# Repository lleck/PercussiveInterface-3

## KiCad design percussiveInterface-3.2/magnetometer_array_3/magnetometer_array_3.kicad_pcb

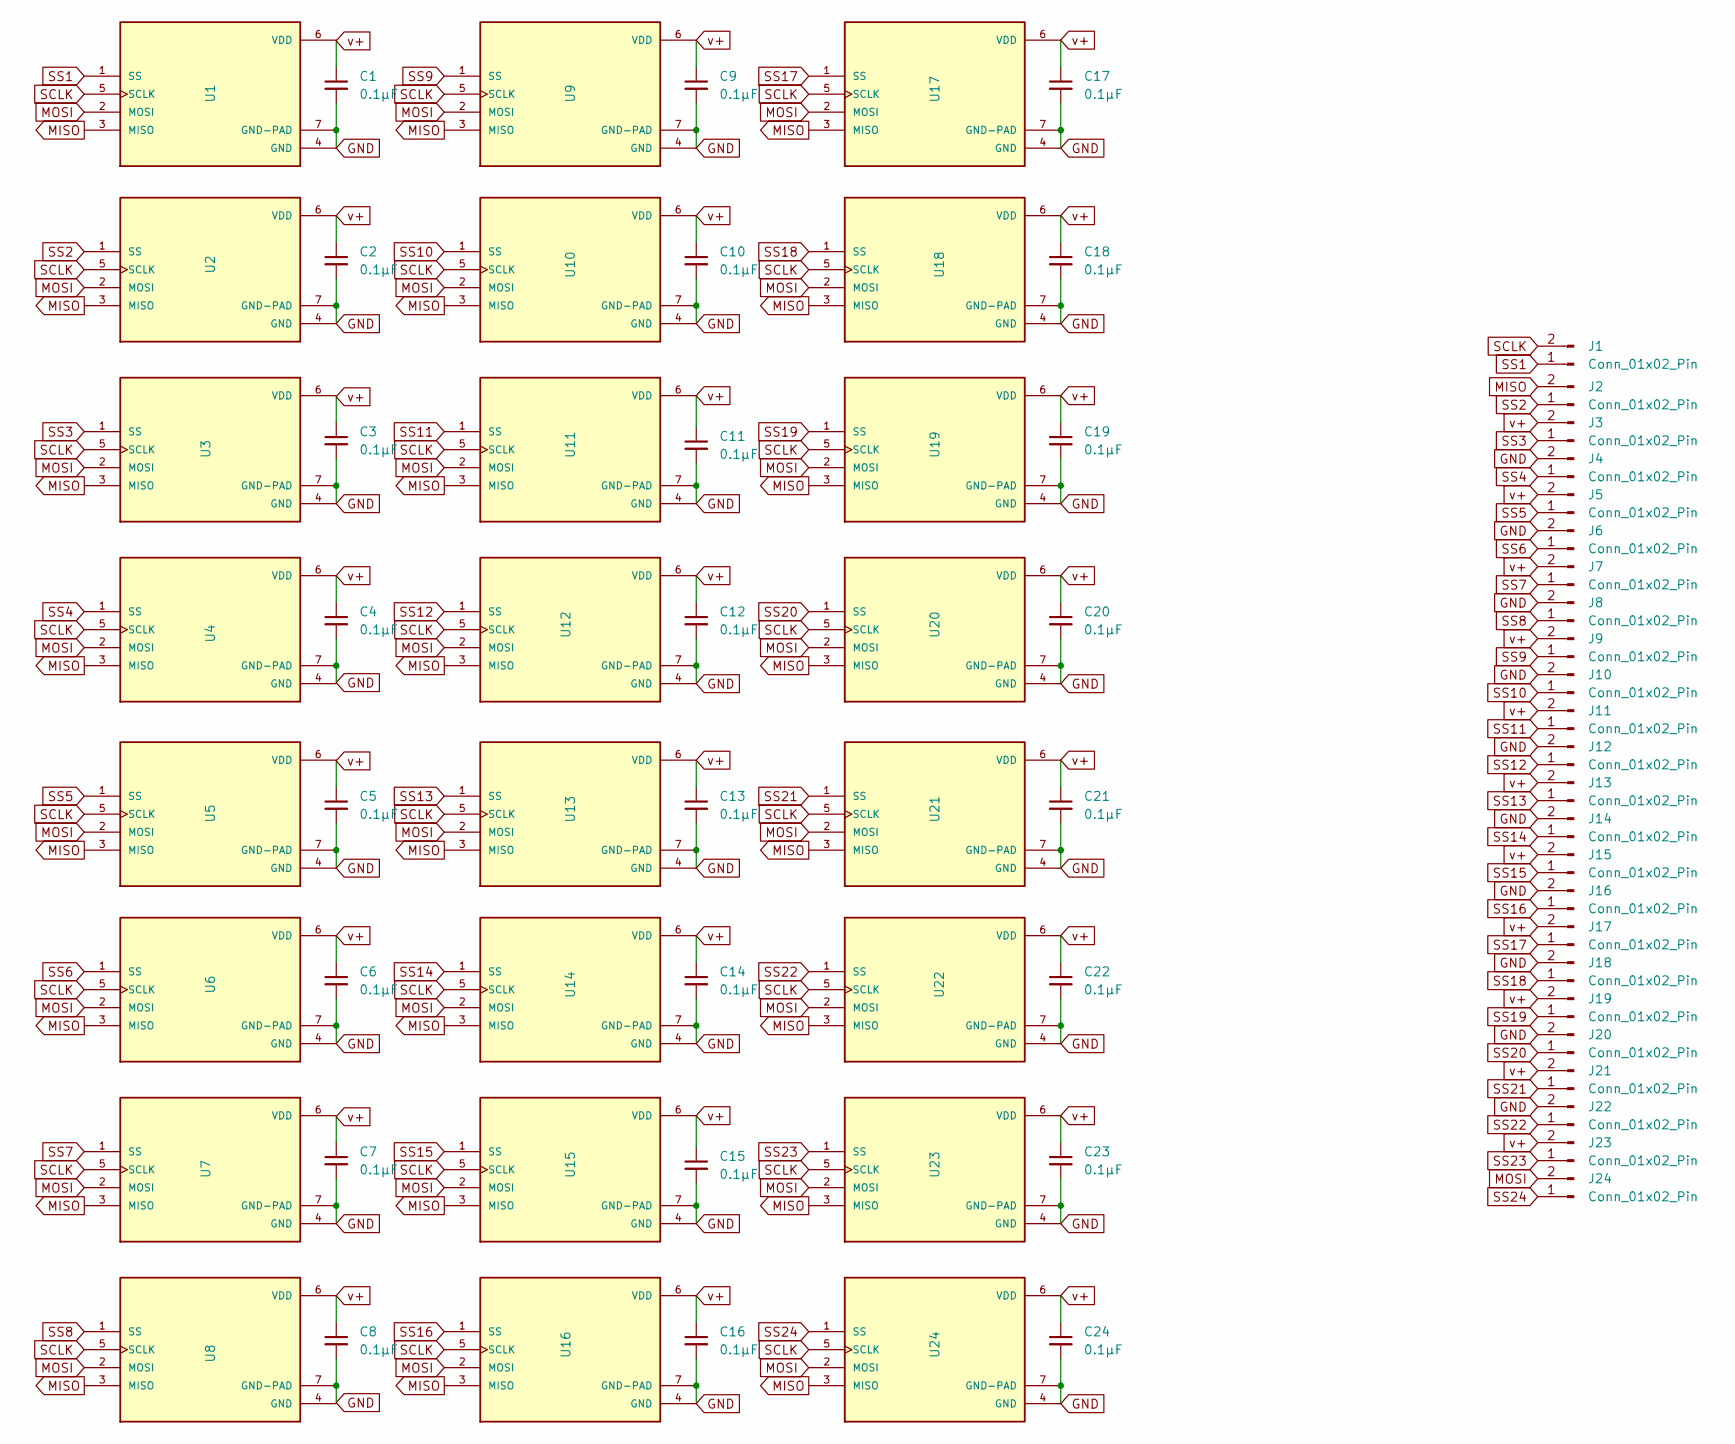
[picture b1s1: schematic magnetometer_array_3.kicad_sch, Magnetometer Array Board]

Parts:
C1, C2, C3, C4, C5, C6, C7, C8, C9, C10, C11, C12, C13, C14, C15, C16, C17, C18, C19, C20, C21, C22, C23, C24: 0.1µF; C_0201_0603Metric
J1, J2, J3, J4, J5, J6, J7, J8, J9, J10, J11, J12, J13, J14, J15, J16, J17, J18, J19, J20, J21, J22, J23, J24: Conn_01x02_Pin; mill_max 328-HORIZONTAL SURFACE MOUNT HEADER
U1, U2, U3, U4, U5, U6, U7, U8, U9, U10, U11, U12, U13, U14, U15, U16, U17, U18, U19, U20, U21, U22, U23, U24: SM225-10E; NVE SM225 10E; PARTREV D

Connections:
GND: C1.2, C2.2, C3.2, C4.2, C5.2, C6.2, C7.2, C8.2, C9.2, C10.2, C11.2, C12.2, C13.2, C14.2, C15.2, C16.2, C17.2, C18.2, C19.2, C20.2, C21.2, C22.2, C23.2, C24.2, J4.2, J6.2, J8.2, J10.2, J12.2, J14.2, J16.2, J18.2, J20.2, J22.2, U1.4 (GND), U1.7 (GND-PAD), U2.4 (GND), U2.7 (GND-PAD), U3.4 (GND), U3.7 (GND-PAD), U4.4 (GND), U4.7 (GND-PAD), U5.4 (GND), U5.7 (GND-PAD), U6.4 (GND), U6.7 (GND-PAD), U7.4 (GND), U7.7 (GND-PAD), U8.4 (GND), U8.7 (GND-PAD), U9.4 (GND), U9.7 (GND-PAD), U10.4 (GND), U10.7 (GND-PAD), U11.4 (GND), U11.7 (GND-PAD), U12.4 (GND), U12.7 (GND-PAD), U13.4 (GND), U13.7 (GND-PAD), U14.4 (GND), U14.7 (GND-PAD), U15.4 (GND), U15.7 (GND-PAD), U16.4 (GND), U16.7 (GND-PAD), U17.4 (GND), U17.7 (GND-PAD), U18.4 (GND), U18.7 (GND-PAD), U19.4 (GND), U19.7 (GND-PAD), U20.4 (GND), U20.7 (GND-PAD), U21.4 (GND), U21.7 (GND-PAD), U22.4 (GND), U22.7 (GND-PAD), U23.4 (GND), U23.7 (GND-PAD), U24.4 (GND), U24.7 (GND-PAD)
MISO: J2.2, U1.3 (MISO), U2.3 (MISO), U3.3 (MISO), U4.3 (MISO), U5.3 (MISO), U6.3 (MISO), U7.3 (MISO), U8.3 (MISO), U9.3 (MISO), U10.3 (MISO), U11.3 (MISO), U12.3 (MISO), U13.3 (MISO), U14.3 (MISO), U15.3 (MISO), U16.3 (MISO), U17.3 (MISO), U18.3 (MISO), U19.3 (MISO), U20.3 (MISO), U21.3 (MISO), U22.3 (MISO), U23.3 (MISO), U24.3 (MISO)
MOSI: J24.2, U1.2 (MOSI), U2.2 (MOSI), U3.2 (MOSI), U4.2 (MOSI), U5.2 (MOSI), U6.2 (MOSI), U7.2 (MOSI), U8.2 (MOSI), U9.2 (MOSI), U10.2 (MOSI), U11.2 (MOSI), U12.2 (MOSI), U13.2 (MOSI), U14.2 (MOSI), U15.2 (MOSI), U16.2 (MOSI), U17.2 (MOSI), U18.2 (MOSI), U19.2 (MOSI), U20.2 (MOSI), U21.2 (MOSI), U22.2 (MOSI), U23.2 (MOSI), U24.2 (MOSI)
SCLK: J1.2, U1.5 (SCLK), U2.5 (SCLK), U3.5 (SCLK), U4.5 (SCLK), U5.5 (SCLK), U6.5 (SCLK), U7.5 (SCLK), U8.5 (SCLK), U9.5 (SCLK), U10.5 (SCLK), U11.5 (SCLK), U12.5 (SCLK), U13.5 (SCLK), U14.5 (SCLK), U15.5 (SCLK), U16.5 (SCLK), U17.5 (SCLK), U18.5 (SCLK), U19.5 (SCLK), U20.5 (SCLK), U21.5 (SCLK), U22.5 (SCLK), U23.5 (SCLK), U24.5 (SCLK)
SS1: J1.1, U1.1 (SS)
SS2: J2.1, U2.1 (SS)
SS3: J3.1, U3.1 (SS)
SS4: J4.1, U4.1 (SS)
SS5: J5.1, U5.1 (SS)
SS6: J6.1, U6.1 (SS)
SS7: J7.1, U7.1 (SS)
SS8: J8.1, U8.1 (SS)
SS9: J9.1, U9.1 (SS)
SS10: J10.1, U10.1 (SS)
SS11: J11.1, U11.1 (SS)
SS12: J12.1, U12.1 (SS)
SS13: J13.1, U13.1 (SS)
SS14: J14.1, U14.1 (SS)
SS15: J15.1, U15.1 (SS)
SS16: J16.1, U16.1 (SS)
SS17: J17.1, U17.1 (SS)
SS18: J18.1, U18.1 (SS)
SS19: J19.1, U19.1 (SS)
SS20: J20.1, U20.1 (SS)
SS21: J21.1, U21.1 (SS)
SS22: J22.1, U22.1 (SS)
SS23: J23.1, U23.1 (SS)
SS24: J24.1, U24.1 (SS)
v+: C1.1, C2.1, C3.1, C4.1, C5.1, C6.1, C7.1, C8.1, C9.1, C10.1, C11.1, C12.1, C13.1, C14.1, C15.1, C16.1, C17.1, C18.1, C19.1, C20.1, C21.1, C22.1, C23.1, C24.1, J3.2, J5.2, J7.2, J9.2, J11.2, J13.2, J15.2, J17.2, J19.2, J21.2, J23.2, U1.6 (VDD), U2.6 (VDD), U3.6 (VDD), U4.6 (VDD), U5.6 (VDD), U6.6 (VDD), U7.6 (VDD), U8.6 (VDD), U9.6 (VDD), U10.6 (VDD), U11.6 (VDD), U12.6 (VDD), U13.6 (VDD), U14.6 (VDD), U15.6 (VDD), U16.6 (VDD), U17.6 (VDD), U18.6 (VDD), U19.6 (VDD), U20.6 (VDD), U21.6 (VDD), U22.6 (VDD), U23.6 (VDD), U24.6 (VDD)

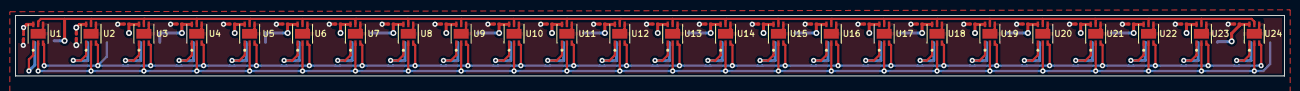
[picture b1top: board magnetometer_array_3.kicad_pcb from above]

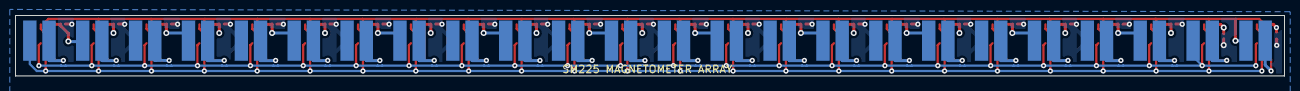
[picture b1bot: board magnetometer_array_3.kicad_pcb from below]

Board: 4 copper layers, 168.0 x 8.0 mm, 72 parts (24 on the bottom side), 29 nets.

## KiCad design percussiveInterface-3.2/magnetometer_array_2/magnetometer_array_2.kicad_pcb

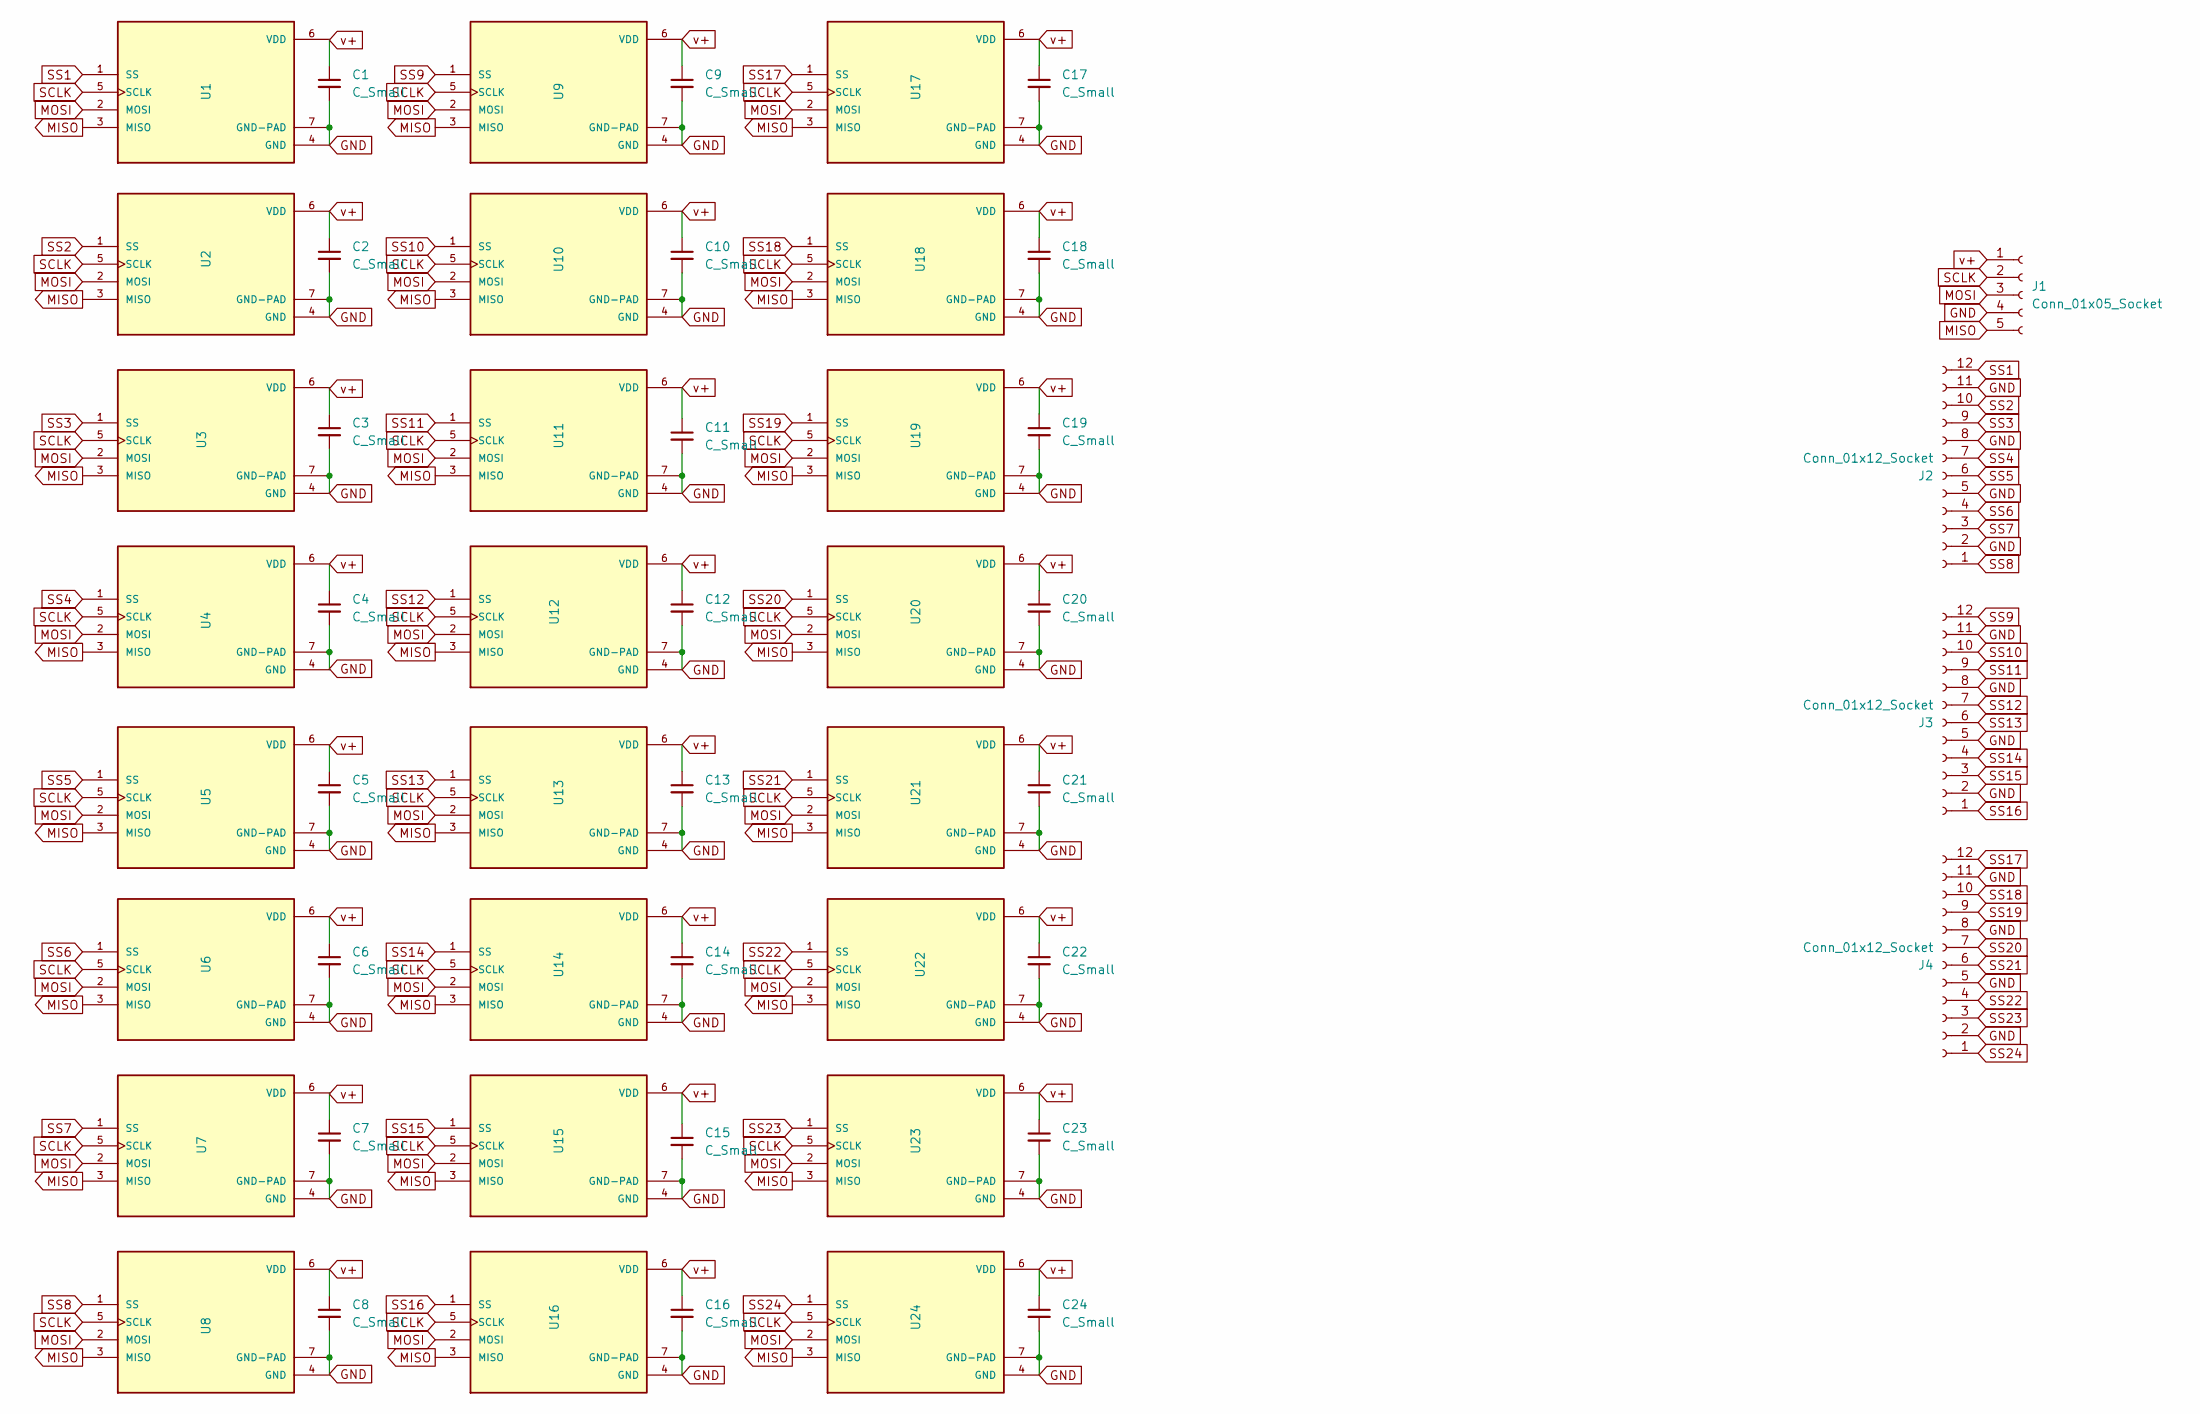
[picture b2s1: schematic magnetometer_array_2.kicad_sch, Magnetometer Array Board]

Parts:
C1, C2, C3, C4, C5, C6, C7, C8, C9, C10, C11, C12, C13, C14, C15, C16, C17, C18, C19, C20, C21, C22, C23, C24: C_Small; C_0201_0603Metric
J1: Conn_01x05_Socket; PinHeader_1x05_P2.54mm_Horizontal
J2, J3, J4: Conn_01x12_Socket; PinHeader_1x12_P2.54mm_Horizontal
U1, U2, U3, U4, U5, U6, U7, U8, U9, U10, U11, U12, U13, U14, U15, U16, U17, U18, U19, U20, U21, U22, U23, U24: SM225-10E; NVE SM225 10E; PARTREV D

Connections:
GND: C1.2, C2.2, C3.2, C4.2, C5.2, C6.2, C7.2, C8.2, C9.2, C10.2, C11.2, C12.2, C13.2, C14.2, C15.2, C16.2, C17.2, C18.2, C19.2, C20.2, C21.2, C22.2, C23.2, C24.2, J1.4, J2.2, J2.5, J2.8, J2.11, J3.2, J3.5, J3.8, J3.11, J4.2, J4.5, J4.8, J4.11, U1.4 (GND), U1.7 (GND-PAD), U2.4 (GND), U2.7 (GND-PAD), U3.4 (GND), U3.7 (GND-PAD), U4.4 (GND), U4.7 (GND-PAD), U5.4 (GND), U5.7 (GND-PAD), U6.4 (GND), U6.7 (GND-PAD), U7.4 (GND), U7.7 (GND-PAD), U8.4 (GND), U8.7 (GND-PAD), U9.4 (GND), U9.7 (GND-PAD), U10.4 (GND), U10.7 (GND-PAD), U11.4 (GND), U11.7 (GND-PAD), U12.4 (GND), U12.7 (GND-PAD), U13.4 (GND), U13.7 (GND-PAD), U14.4 (GND), U14.7 (GND-PAD), U15.4 (GND), U15.7 (GND-PAD), U16.4 (GND), U16.7 (GND-PAD), U17.4 (GND), U17.7 (GND-PAD), U18.4 (GND), U18.7 (GND-PAD), U19.4 (GND), U19.7 (GND-PAD), U20.4 (GND), U20.7 (GND-PAD), U21.4 (GND), U21.7 (GND-PAD), U22.4 (GND), U22.7 (GND-PAD), U23.4 (GND), U23.7 (GND-PAD), U24.4 (GND), U24.7 (GND-PAD)
MISO: J1.5, U1.3 (MISO), U2.3 (MISO), U3.3 (MISO), U4.3 (MISO), U5.3 (MISO), U6.3 (MISO), U7.3 (MISO), U8.3 (MISO), U9.3 (MISO), U10.3 (MISO), U11.3 (MISO), U12.3 (MISO), U13.3 (MISO), U14.3 (MISO), U15.3 (MISO), U16.3 (MISO), U17.3 (MISO), U18.3 (MISO), U19.3 (MISO), U20.3 (MISO), U21.3 (MISO), U22.3 (MISO), U23.3 (MISO), U24.3 (MISO)
MOSI: J1.3, U1.2 (MOSI), U2.2 (MOSI), U3.2 (MOSI), U4.2 (MOSI), U5.2 (MOSI), U6.2 (MOSI), U7.2 (MOSI), U8.2 (MOSI), U9.2 (MOSI), U10.2 (MOSI), U11.2 (MOSI), U12.2 (MOSI), U13.2 (MOSI), U14.2 (MOSI), U15.2 (MOSI), U16.2 (MOSI), U17.2 (MOSI), U18.2 (MOSI), U19.2 (MOSI), U20.2 (MOSI), U21.2 (MOSI), U22.2 (MOSI), U23.2 (MOSI), U24.2 (MOSI)
SCLK: J1.2, U1.5 (SCLK), U2.5 (SCLK), U3.5 (SCLK), U4.5 (SCLK), U5.5 (SCLK), U6.5 (SCLK), U7.5 (SCLK), U8.5 (SCLK), U9.5 (SCLK), U10.5 (SCLK), U11.5 (SCLK), U12.5 (SCLK), U13.5 (SCLK), U14.5 (SCLK), U15.5 (SCLK), U16.5 (SCLK), U17.5 (SCLK), U18.5 (SCLK), U19.5 (SCLK), U20.5 (SCLK), U21.5 (SCLK), U22.5 (SCLK), U23.5 (SCLK), U24.5 (SCLK)
SS1: J2.12, U1.1 (SS)
SS2: J2.10, U2.1 (SS)
SS3: J2.9, U3.1 (SS)
SS4: J2.7, U4.1 (SS)
SS5: J2.6, U5.1 (SS)
SS6: J2.4, U6.1 (SS)
SS7: J2.3, U7.1 (SS)
SS8: J2.1, U8.1 (SS)
SS9: J3.12, U9.1 (SS)
SS10: J3.10, U10.1 (SS)
SS11: J3.9, U11.1 (SS)
SS12: J3.7, U12.1 (SS)
SS13: J3.6, U13.1 (SS)
SS14: J3.4, U14.1 (SS)
SS15: J3.3, U15.1 (SS)
SS16: J3.1, U16.1 (SS)
SS17: J4.12, U17.1 (SS)
SS18: J4.10, U18.1 (SS)
SS19: J4.9, U19.1 (SS)
SS20: J4.7, U20.1 (SS)
SS21: J4.6, U21.1 (SS)
SS22: J4.4, U22.1 (SS)
SS23: J4.3, U23.1 (SS)
SS24: J4.1, U24.1 (SS)
v+: C1.1, C2.1, C3.1, C4.1, C5.1, C6.1, C7.1, C8.1, C9.1, C10.1, C11.1, C12.1, C13.1, C14.1, C15.1, C16.1, C17.1, C18.1, C19.1, C20.1, C21.1, C22.1, C23.1, C24.1, J1.1, U1.6 (VDD), U2.6 (VDD), U3.6 (VDD), U4.6 (VDD), U5.6 (VDD), U6.6 (VDD), U7.6 (VDD), U8.6 (VDD), U9.6 (VDD), U10.6 (VDD), U11.6 (VDD), U12.6 (VDD), U13.6 (VDD), U14.6 (VDD), U15.6 (VDD), U16.6 (VDD), U17.6 (VDD), U18.6 (VDD), U19.6 (VDD), U20.6 (VDD), U21.6 (VDD), U22.6 (VDD), U23.6 (VDD), U24.6 (VDD)

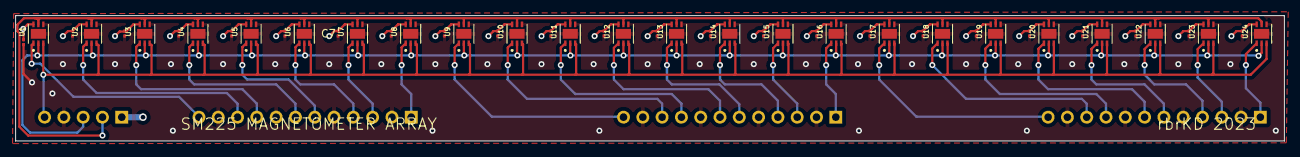
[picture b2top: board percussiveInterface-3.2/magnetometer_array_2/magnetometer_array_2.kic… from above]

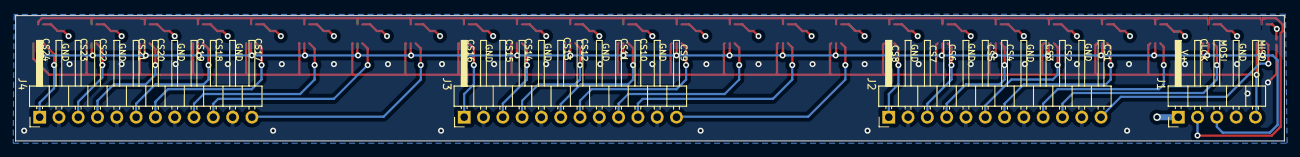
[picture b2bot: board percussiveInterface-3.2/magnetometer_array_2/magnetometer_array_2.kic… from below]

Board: 4 copper layers, 167.0 x 16.5 mm, 52 parts (4 on the bottom side), 29 nets.

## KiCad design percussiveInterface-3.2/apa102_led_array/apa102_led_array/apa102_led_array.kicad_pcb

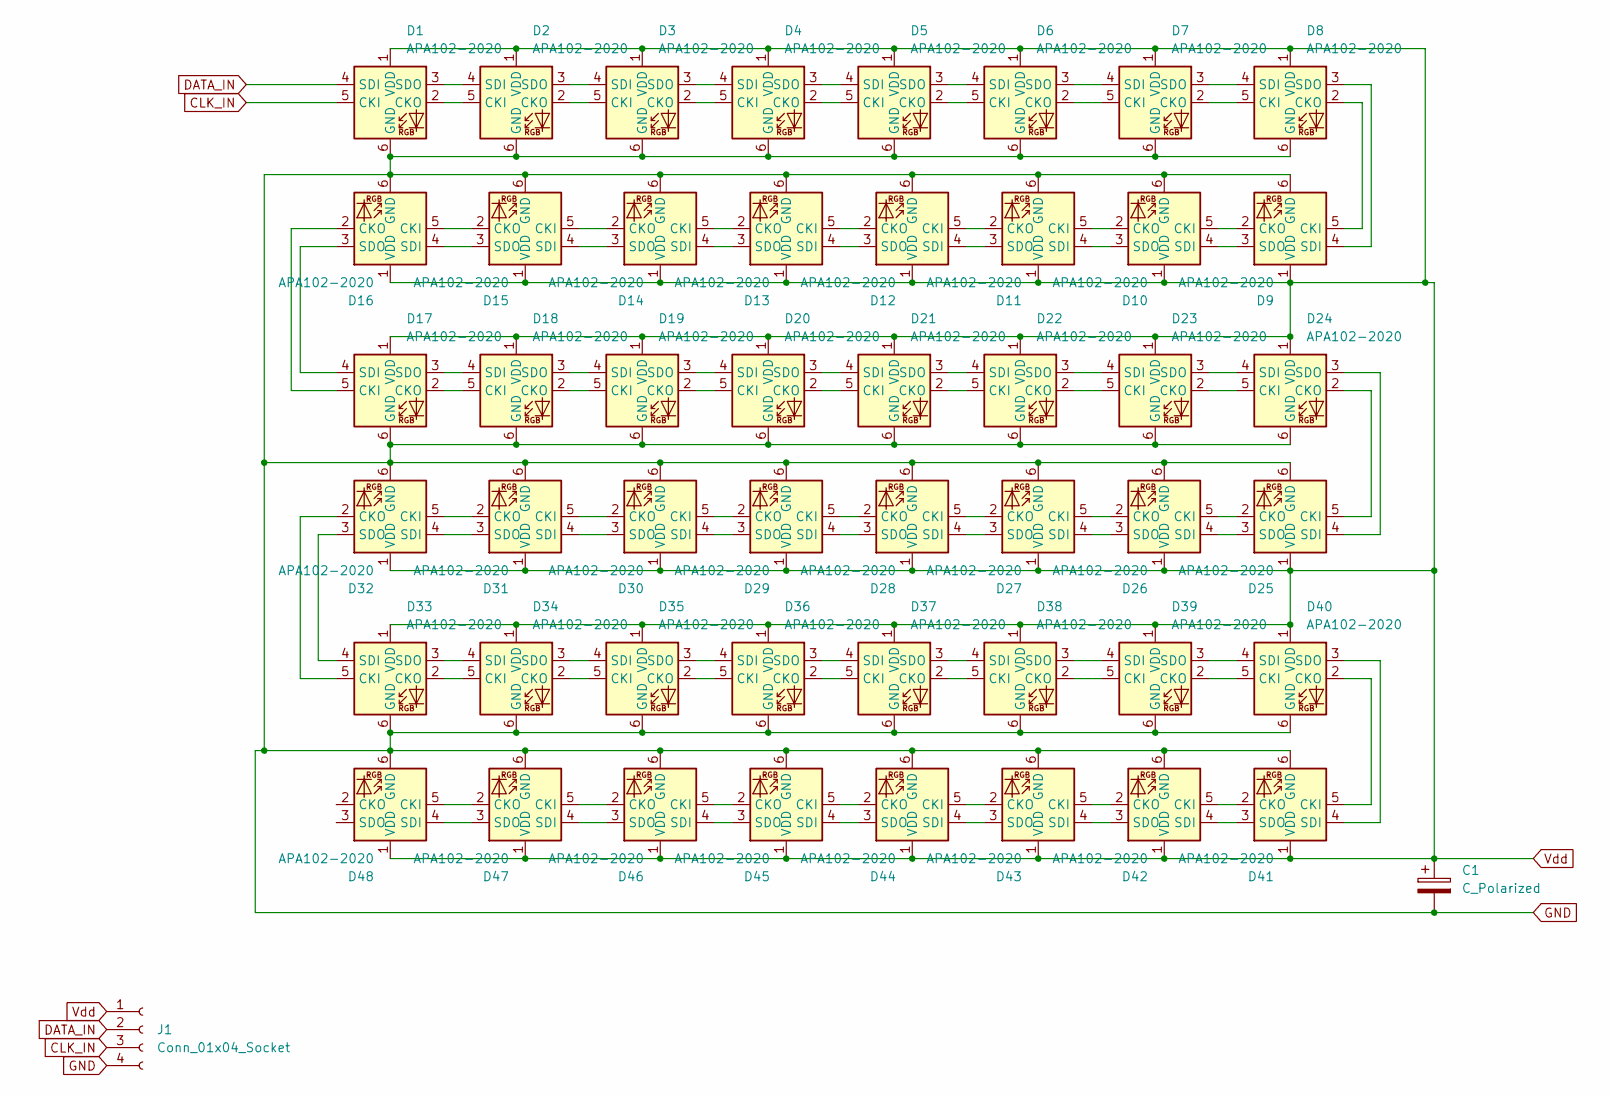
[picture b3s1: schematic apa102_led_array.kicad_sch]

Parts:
C1: C_Polarized; CP_EIA-7343-15_Kemet-W
D1, D2, D3, D4, D5, D6, D7, D8, D9, D10, D11, D12, D13, D14, D15, D16, D17, D18, D19, D20, D21, D22, D23, D24, D25, D26, D27, D28, D29, D30, D31, D32, D33, D34, D35, D36, D37, D38, D39, D40, D41, D42, D43, D44, D45, D46, D47, D48: APA102-2020; LED-APA102-2020
J1: Conn_01x04_Socket; Pin_D0.7mm_L6.5mm_W1.8mm_FlatFork

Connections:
CLK_IN: D1.5 (CKI), D48.2 (CKO), J1.3
DATA_IN: D1.4 (SDI), D48.3 (SDO), J1.2
GND: C1.2, D1.6 (GND), D2.6 (GND), D3.6 (GND), D4.6 (GND), D5.6 (GND), D6.6 (GND), D7.6 (GND), D8.6 (GND), D9.6 (GND), D10.6 (GND), D11.6 (GND), D12.6 (GND), D13.6 (GND), D14.6 (GND), D15.6 (GND), D16.6 (GND), D17.6 (GND), D18.6 (GND), D19.6 (GND), D20.6 (GND), D21.6 (GND), D22.6 (GND), D23.6 (GND), D24.6 (GND), D25.6 (GND), D26.6 (GND), D27.6 (GND), D28.6 (GND), D29.6 (GND), D30.6 (GND), D31.6 (GND), D32.6 (GND), D33.6 (GND), D34.6 (GND), D35.6 (GND), D36.6 (GND), D37.6 (GND), D38.6 (GND), D39.6 (GND), D40.6 (GND), D41.6 (GND), D42.6 (GND), D43.6 (GND), D44.6 (GND), D45.6 (GND), D46.6 (GND), D47.6 (GND), D48.6 (GND), J1.4
unnamed: D1.2 (CKO), D2.5 (CKI)
unnamed: D1.3 (SDO), D2.4 (SDI)
unnamed: D2.2 (CKO), D3.5 (CKI)
unnamed: D2.3 (SDO), D3.4 (SDI)
unnamed: D3.2 (CKO), D4.5 (CKI)
unnamed: D3.3 (SDO), D4.4 (SDI)
unnamed: D4.2 (CKO), D5.5 (CKI)
unnamed: D4.3 (SDO), D5.4 (SDI)
unnamed: D5.2 (CKO), D6.5 (CKI)
unnamed: D5.3 (SDO), D6.4 (SDI)
unnamed: D6.2 (CKO), D7.5 (CKI)
unnamed: D6.3 (SDO), D7.4 (SDI)
unnamed: D7.2 (CKO), D8.5 (CKI)
unnamed: D7.3 (SDO), D8.4 (SDI)
unnamed: D8.2 (CKO), D9.5 (CKI)
unnamed: D8.3 (SDO), D9.4 (SDI)
unnamed: D9.2 (CKO), D10.5 (CKI)
unnamed: D10.2 (CKO), D11.5 (CKI)
unnamed: D9.3 (SDO), D10.4 (SDI)
unnamed: D10.3 (SDO), D11.4 (SDI)
unnamed: D11.2 (CKO), D12.5 (CKI)
unnamed: D11.3 (SDO), D12.4 (SDI)
unnamed: D12.2 (CKO), D13.5 (CKI)
unnamed: D12.3 (SDO), D13.4 (SDI)
unnamed: D13.2 (CKO), D14.5 (CKI)
unnamed: D13.3 (SDO), D14.4 (SDI)
unnamed: D14.2 (CKO), D15.5 (CKI)
unnamed: D14.3 (SDO), D15.4 (SDI)
unnamed: D15.2 (CKO), D16.5 (CKI)
unnamed: D15.3 (SDO), D16.4 (SDI)
unnamed: D16.2 (CKO), D17.5 (CKI)
unnamed: D16.3 (SDO), D17.4 (SDI)
unnamed: D17.2 (CKO), D18.5 (CKI)
unnamed: D17.3 (SDO), D18.4 (SDI)
unnamed: D18.2 (CKO), D19.5 (CKI)
unnamed: D18.3 (SDO), D19.4 (SDI)
unnamed: D19.2 (CKO), D20.5 (CKI)
unnamed: D19.3 (SDO), D20.4 (SDI)
unnamed: D20.2 (CKO), D21.5 (CKI)
unnamed: D20.3 (SDO), D21.4 (SDI)
unnamed: D21.2 (CKO), D22.5 (CKI)
unnamed: D21.3 (SDO), D22.4 (SDI)
unnamed: D22.2 (CKO), D23.5 (CKI)
unnamed: D22.3 (SDO), D23.4 (SDI)
unnamed: D23.2 (CKO), D24.5 (CKI)
unnamed: D23.3 (SDO), D24.4 (SDI)
unnamed: D24.2 (CKO), D25.5 (CKI)
unnamed: D24.3 (SDO), D25.4 (SDI)
unnamed: D25.2 (CKO), D26.5 (CKI)
unnamed: D25.3 (SDO), D26.4 (SDI)
unnamed: D26.2 (CKO), D27.5 (CKI)
unnamed: D26.3 (SDO), D27.4 (SDI)
unnamed: D27.2 (CKO), D28.5 (CKI)
unnamed: D27.3 (SDO), D28.4 (SDI)
unnamed: D28.2 (CKO), D29.5 (CKI)
unnamed: D28.3 (SDO), D29.4 (SDI)
unnamed: D29.2 (CKO), D30.5 (CKI)
unnamed: D29.3 (SDO), D30.4 (SDI)
unnamed: D30.2 (CKO), D31.5 (CKI)
unnamed: D30.3 (SDO), D31.4 (SDI)
unnamed: D31.2 (CKO), D32.5 (CKI)
unnamed: D31.3 (SDO), D32.4 (SDI)
unnamed: D32.2 (CKO), D33.5 (CKI)
unnamed: D32.3 (SDO), D33.4 (SDI)
unnamed: D33.2 (CKO), D34.5 (CKI)
unnamed: D33.3 (SDO), D34.4 (SDI)
unnamed: D34.2 (CKO), D35.5 (CKI)
unnamed: D34.3 (SDO), D35.4 (SDI)
unnamed: D35.2 (CKO), D36.5 (CKI)
unnamed: D35.3 (SDO), D36.4 (SDI)
unnamed: D36.2 (CKO), D37.5 (CKI)
unnamed: D36.3 (SDO), D37.4 (SDI)
unnamed: D37.2 (CKO), D38.5 (CKI)
unnamed: D37.3 (SDO), D38.4 (SDI)
unnamed: D38.2 (CKO), D39.5 (CKI)
unnamed: D38.3 (SDO), D39.4 (SDI)
unnamed: D39.2 (CKO), D40.5 (CKI)
unnamed: D39.3 (SDO), D40.4 (SDI)
unnamed: D40.2 (CKO), D41.5 (CKI)
unnamed: D40.3 (SDO), D41.4 (SDI)
unnamed: D41.2 (CKO), D42.5 (CKI)
unnamed: D41.3 (SDO), D42.4 (SDI)
unnamed: D42.2 (CKO), D43.5 (CKI)
unnamed: D42.3 (SDO), D43.4 (SDI)
unnamed: D43.2 (CKO), D44.5 (CKI)
unnamed: D43.3 (SDO), D44.4 (SDI)
unnamed: D44.2 (CKO), D45.5 (CKI)
unnamed: D44.3 (SDO), D45.4 (SDI)
unnamed: D45.2 (CKO), D46.5 (CKI)
unnamed: D45.3 (SDO), D46.4 (SDI)
unnamed: D46.2 (CKO), D47.5 (CKI)
unnamed: D46.3 (SDO), D47.4 (SDI)
unnamed: D47.2 (CKO), D48.5 (CKI)
unnamed: D47.3 (SDO), D48.4 (SDI)
Vdd: C1.1, D1.1 (VDD), D2.1 (VDD), D3.1 (VDD), D4.1 (VDD), D5.1 (VDD), D6.1 (VDD), D7.1 (VDD), D8.1 (VDD), D9.1 (VDD), D10.1 (VDD), D11.1 (VDD), D12.1 (VDD), D13.1 (VDD), D14.1 (VDD), D15.1 (VDD), D16.1 (VDD), D17.1 (VDD), D18.1 (VDD), D19.1 (VDD), D20.1 (VDD), D21.1 (VDD), D22.1 (VDD), D23.1 (VDD), D24.1 (VDD), D25.1 (VDD), D26.1 (VDD), D27.1 (VDD), D28.1 (VDD), D29.1 (VDD), D30.1 (VDD), D31.1 (VDD), D32.1 (VDD), D33.1 (VDD), D34.1 (VDD), D35.1 (VDD), D36.1 (VDD), D37.1 (VDD), D38.1 (VDD), D39.1 (VDD), D40.1 (VDD), D41.1 (VDD), D42.1 (VDD), D43.1 (VDD), D44.1 (VDD), D45.1 (VDD), D46.1 (VDD), D47.1 (VDD), D48.1 (VDD), J1.1

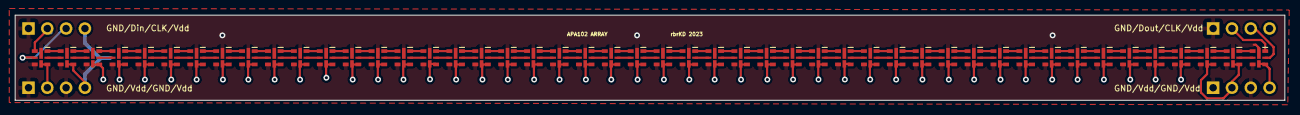
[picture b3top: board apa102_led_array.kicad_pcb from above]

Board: 4 copper layers, 171.5 x 11.5 mm, 49 parts (1 on the bottom side), 98 nets.

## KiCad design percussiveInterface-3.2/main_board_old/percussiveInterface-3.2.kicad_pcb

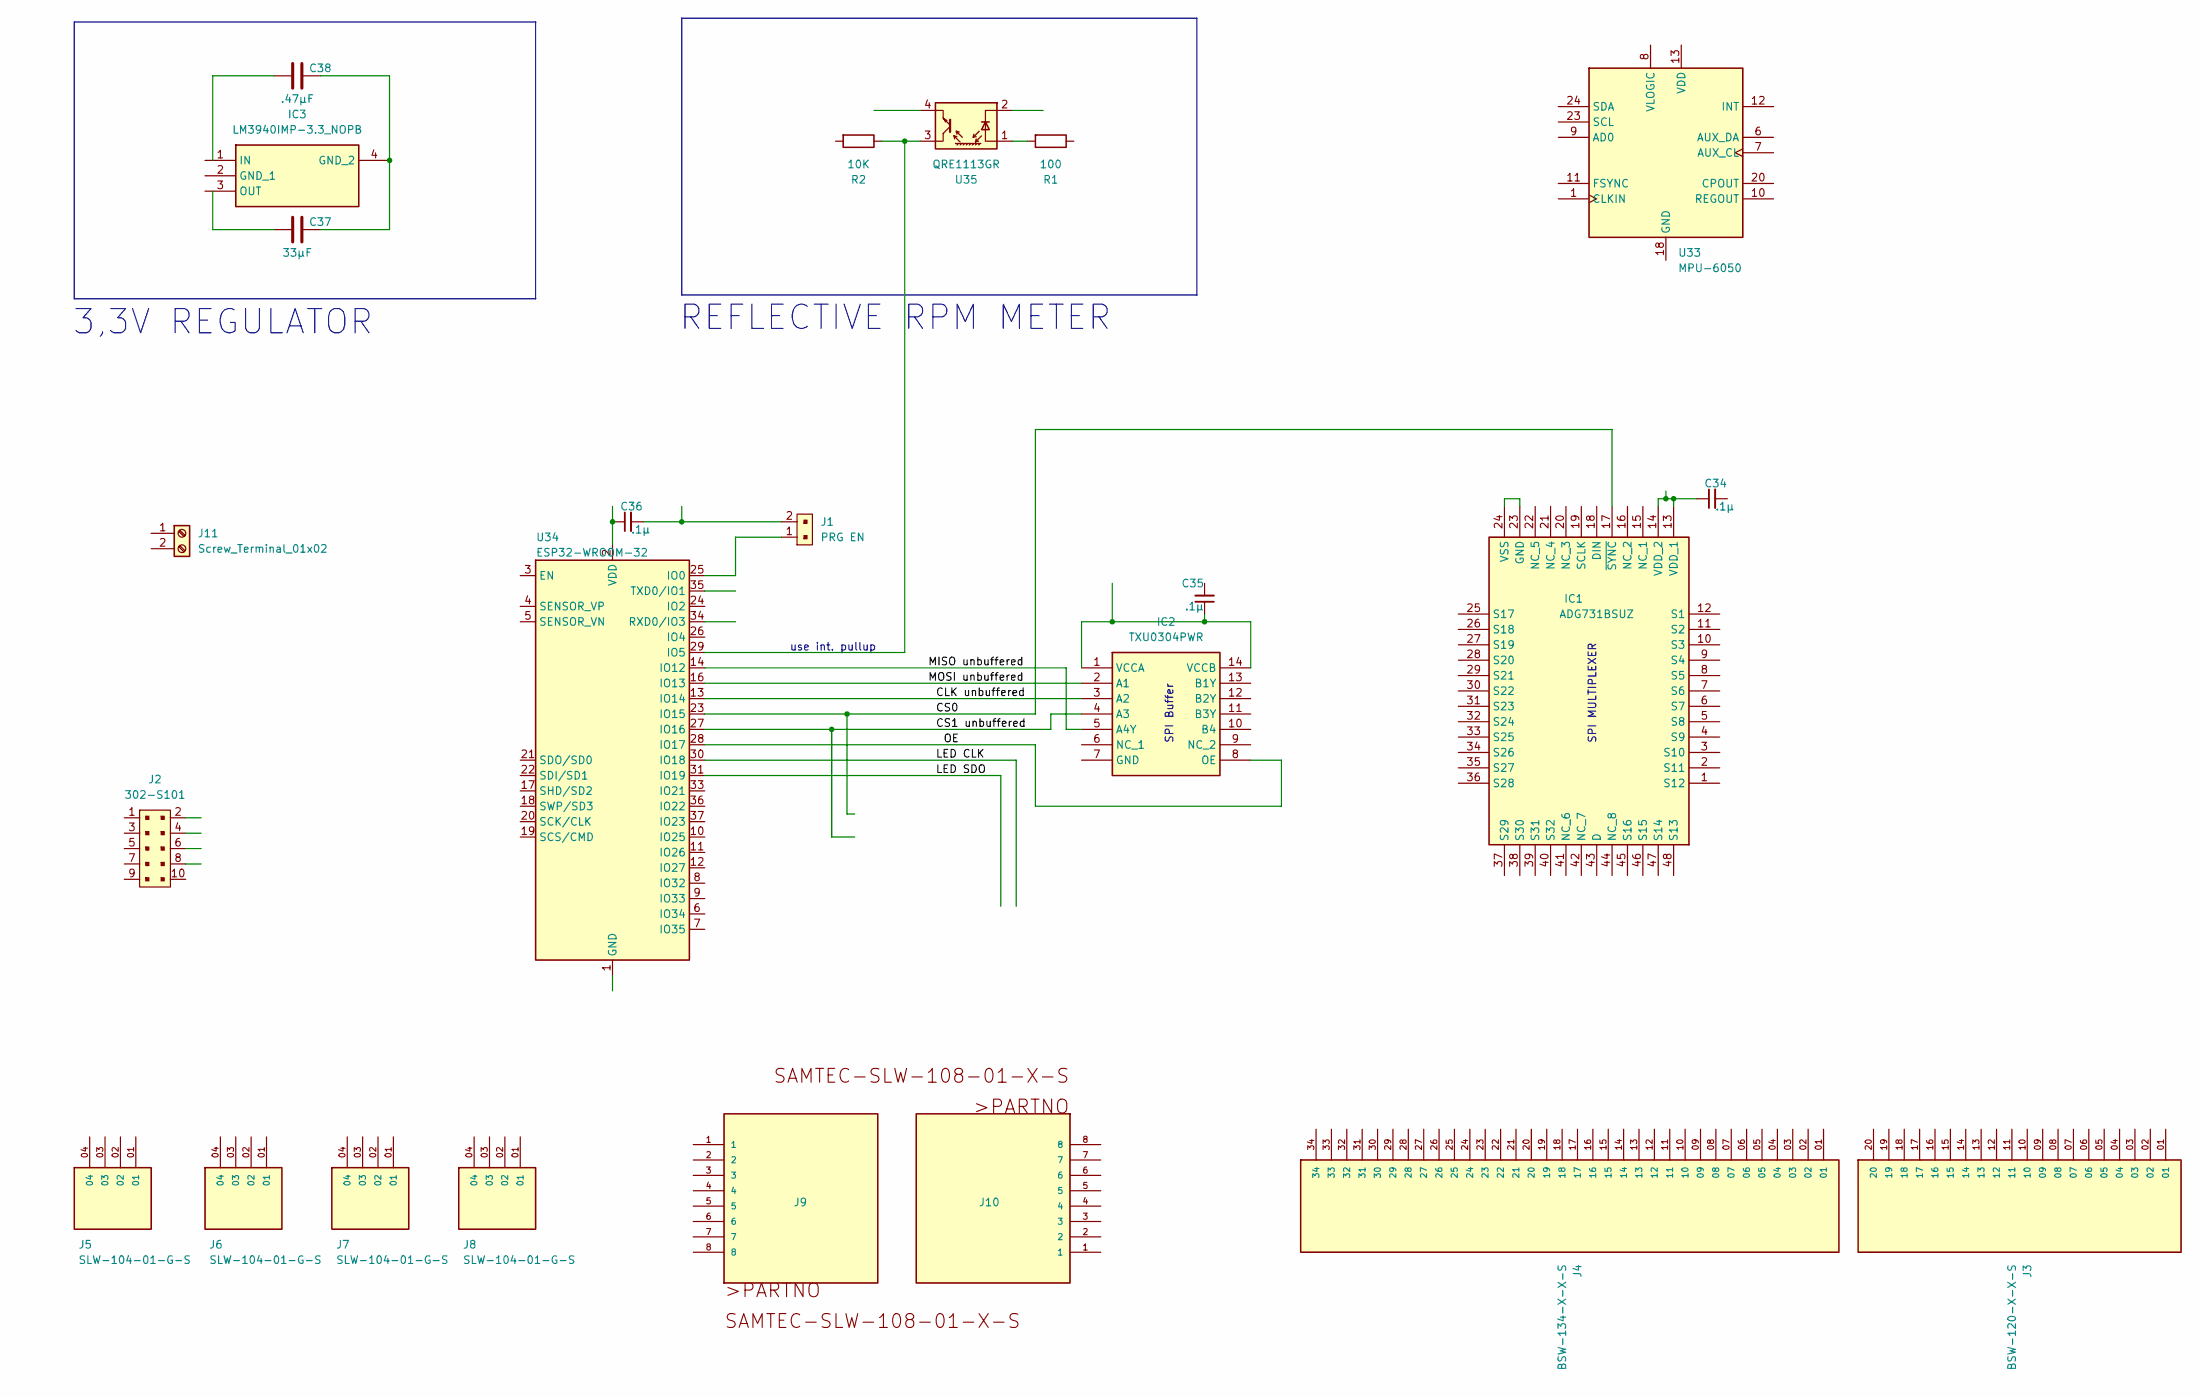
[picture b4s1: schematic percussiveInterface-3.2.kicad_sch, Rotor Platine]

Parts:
C34, C35, C36: .1µ; C_0201_0603Metric
C37: 33µF; C_0402_1005Metric
C38: .47µF; C_0402_1005Metric
IC1: ADG731BSUZ; TQFP48; Manufacturer_Part_Number ADG731BSUZ; Mouser Part Number 584-ADG731BSUZ
IC2: TXU0304PWR; TSSOP-14_4.4x5mm_P0.65mm; Manufacturer_Part_Number TXU0304PWR; Mouser Part Number 595-TXU0304PWR
IC3: LM3940IMP-3.3_NOPB; SOT-223; Manufacturer_Part_Number LM3940IMP-3.3/NOPB; Mouser Part Number 926-LM3940IMP3.3NOPB
J1: PRG EN; PinHeader_1x2_P2.54mm_Drill1.02mm; MPN 22-23-2021; Digi-Key_PN WM4200-ND
J2: 302-S101; PinHeader_2x5_P2.54mm_Drill1.2mm; MPN 302-S101; Digi-Key_PN ED1543-ND
J3: BSW-120-X-X-S; SAMTEC_BSW-120-X-X-S
J4: BSW-134-X-X-S; SAMTEC_BSW-134-X-X-S
J5, J6, J7, J8: SLW-104-01-G-S; SAMTEC_SLW-104-01-G-S; PARTREV B
J9, J10: SAMTEC-SLW-108-01-X-S
J11: Screw_Terminal_01x02; TerminalBlock_Phoenix_MKDS-1,5-2-5.08_1x02_P5.08mm_Horizont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
R1: 100; R_0402_1005Metric
R2: 10K; R_0402_1005Metric
U33: MPU-6050; InvenSense_QFN-24_4x4mm_P0.5mm
U34: ESP32-WROOM-32
U35: QRE1113GR; OnSemi_CASE100CY

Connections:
/CLK unbuffered: IC2.3 (A2), U34.13 (IO14)
/CS0: IC1.17 (~SYNC), U34.23 (IO15)
/CS1 unbuffered: IC2.4 (A3), U34.27 (IO16)
/LED CLK: U34.30 (IO18)
/LED SDO: U34.31 (IO19)
/MISO unbuffered: IC2.5 (A4Y), U34.14 (IO12)
/MOSI unbuffered: IC2.2 (A1), U34.16 (IO13)
/OE: IC2.8 (OE), U34.28 (IO17)
unnamed: C36.2, J1.2
unnamed: IC1.23 (GND), IC1.24 (VSS)
unnamed: C34.1, IC1.13 (VDD_1), IC1.14 (VDD_2)
unnamed: C35.1, IC2.1 (VCCA), IC2.14 (VCCB)
unnamed: C37.2, C38.2, IC3.4 (GND_2)
unnamed: U34.1 (GND), U34.15 (GND), U34.38 (GND), U34.39 (GND)
unnamed: J1.1, U34.25 (IO0)
unnamed: R2.1, U34.29 (IO5), U35.3
unnamed: C36.1, U34.2 (VDD)
unnamed: R1.2, U35.1 (A)

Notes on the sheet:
SPI MULTIPLEXER
REFLECTIVE RPM METER
use int. pullup
3,3V REGULATOR
SPI Buffer

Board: 2 copper layers, 24 parts (0 on the bottom side), 16 nets, no tracks yet.

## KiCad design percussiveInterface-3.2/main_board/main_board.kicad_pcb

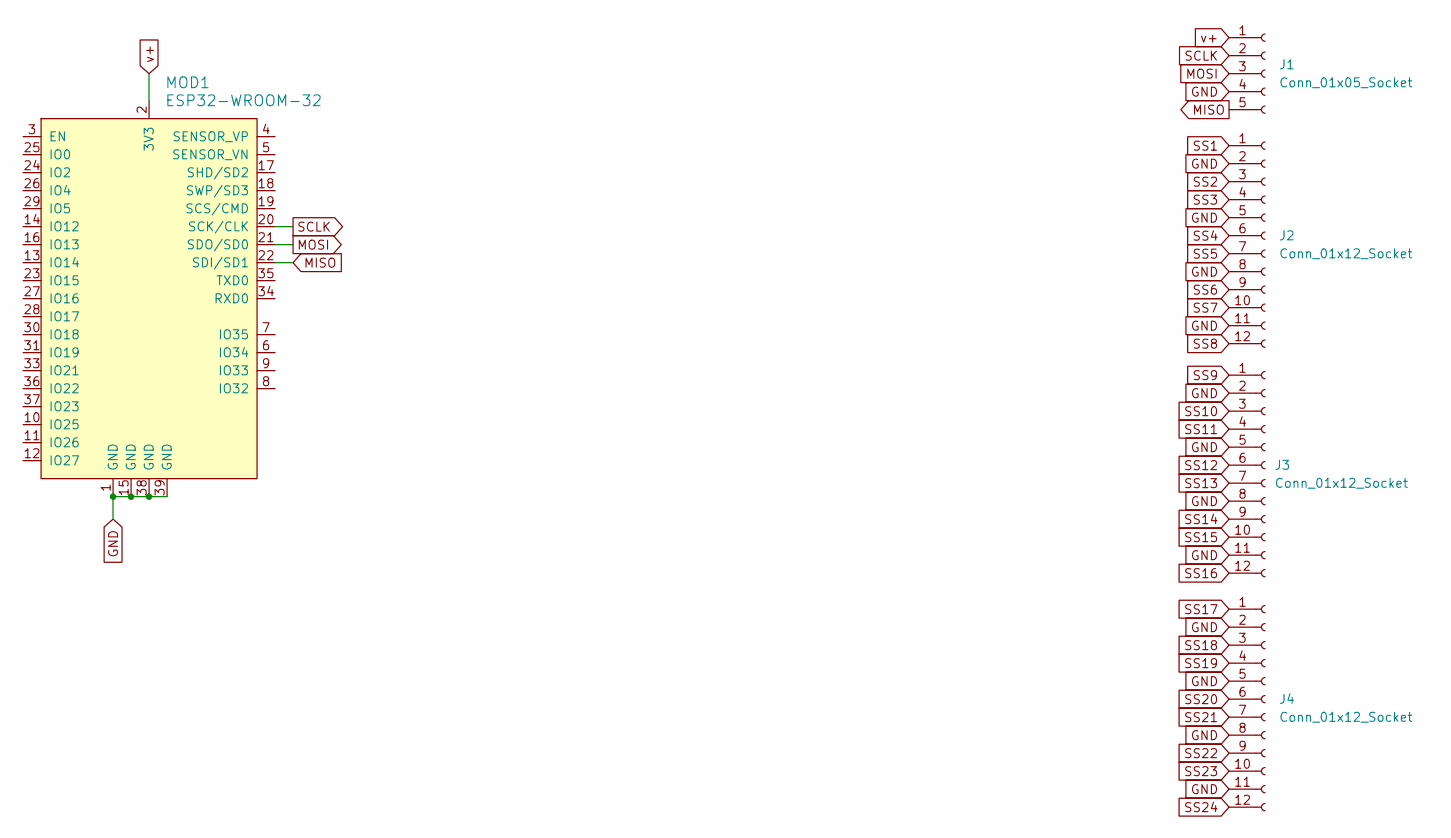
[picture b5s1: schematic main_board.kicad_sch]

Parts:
J1: Conn_01x05_Socket; Hirose_MDF7-05S-2.54DSA(55)
J2, J3, J4: Conn_01x12_Socket; Hirose_MDF7-12S-2.54DSA(55)
MOD1: ESP32-WROOM-32; ESP32-WROOM-32D; MPN ESP32-WROOM-32; Digi-Key_PN 1904-1010-1-ND

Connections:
GND: J1.4, J2.2, J2.5, J2.8, J2.11, J3.2, J3.5, J3.8, J3.11, J4.2, J4.5, J4.8, J4.11, MOD1.1 (GND), MOD1.15 (GND), MOD1.38 (GND), MOD1.39 (GND)
MISO: J1.5, MOD1.22 (SDI/SD1)
MOSI: J1.3, MOD1.21 (SDO/SD0)
SCLK: J1.2, MOD1.20 (SCK/CLK)
SS1: J2.1
SS2: J2.3
SS3: J2.4
SS4: J2.6
SS5: J2.7
SS6: J2.9
SS7: J2.10
SS8: J2.12
SS9: J3.1
SS10: J3.3
SS11: J3.4
SS12: J3.6
SS13: J3.7
SS14: J3.9
SS15: J3.10
SS16: J3.12
SS17: J4.1
SS18: J4.3
SS19: J4.4
SS20: J4.6
SS21: J4.7
SS22: J4.9
SS23: J4.10
SS24: J4.12
v+: J1.1, MOD1.2 (3V3)

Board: 2 copper layers, 5 parts (0 on the bottom side), 5 nets, no tracks yet.
